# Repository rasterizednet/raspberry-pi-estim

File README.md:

# Raspberry Pi Estim

This repo includes kicad projects for the raspbi controller, and estim breakout, as well as the AVR source code for the estim breakout.

This is an untested prototype. More information can be found at [Schnizel Wolf: Raspberry PI Estim Breakout](https://schnitzelwolf.org/20/raspberry-pi-estim-breakout/)

Feel free to post ideas and recommendations on the Issue Board.

# LICENSE

CC0 1.0 Universal

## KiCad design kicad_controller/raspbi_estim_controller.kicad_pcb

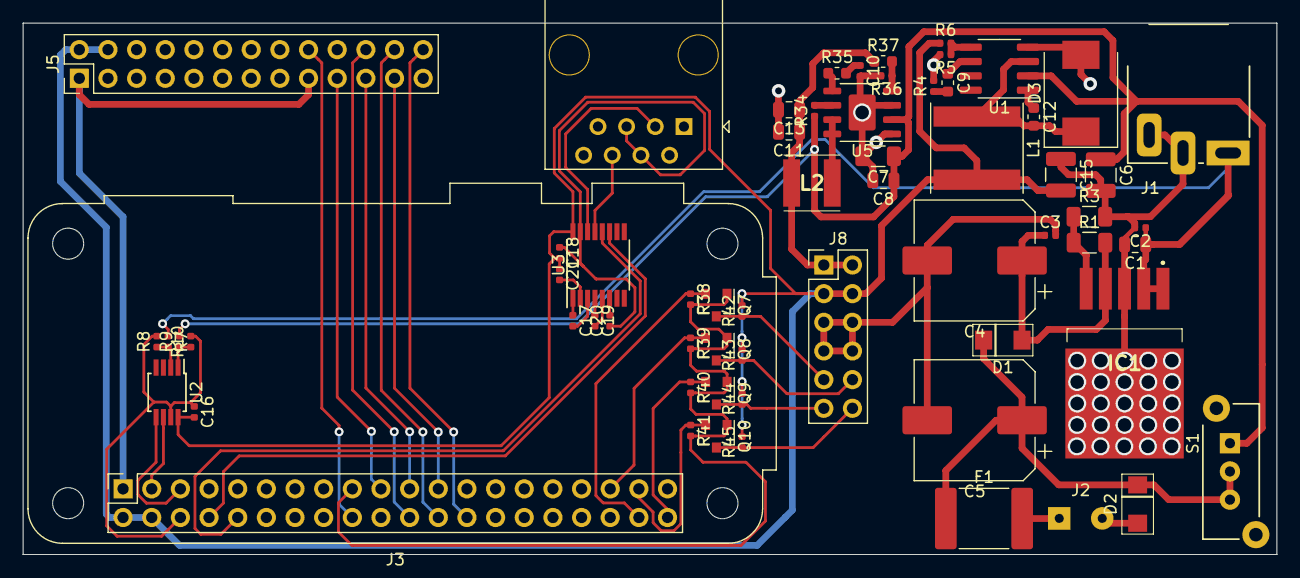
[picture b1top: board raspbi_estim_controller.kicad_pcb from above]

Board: 2 copper layers, 111.1 x 47.1 mm, 63 parts (0 on the bottom side), 49 nets.

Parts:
C1: 10uF; C_0805_2012Metric
C2, C3, C16, C18: 0.1uF; C_0402_1005Metric
C4, C5: 1000uF; CP_Elec_10x12.5
C6: 10uF 35V; C_1210_3225Metric
C7: 10uF 25VDC; C_1206_3216Metric
C8: 0.1uF 50VDC; C_0805_2012Metric
C9: 2.2nF 6.3V; C_0603_1608Metric
C10: 4700pF; C_0402_1005Metric
C11, C13: 22uF 16V; C_0805_2012Metric
C12: 10nF 50V; C_0603_1608Metric
C15: 22uF 10V; C_1210_3225Metric
C17, C19, C20, C21: 1uF; C_0402_1005Metric
D1, D2: 583-FM4004W-W; DO-214AC
D3: B340C/40V, 3A, SMB; D_SMC
F1: 1A Polyfuse; Fuse_2920_7451Metric
IC1: LD29300P2MTR
J1: Barrel_Jack_MountingPin; DJ_Jack_PJ-003A
J2: +12V Battery; SolderWirePad_1x02_P3.81mm_Drill0.8mm
J3: Raspberry_Pi_2_3; Raspberry_Pi_Zero_Socketed_THT_FaceDown_MountingHoles
J4: RJ45; RJ45_OST_PJ012-8P8CX_Vertical
J5: Conn_01x26_Male; PinHeader_2x13_P2.54mm_Vertical
J8: Conn_01x12_Male; estim_breakout
L1: 15uH 2.4A; L_Taiyo-Yuden_NR-80xx
L2: 4.7uH; SRN5040TA4R7M
Q7, Q8, Q9, Q10: BSS138; SOT-23
R1: 100K; R_1206_3216Metric
R3: 7.87K; R_1206_3216Metric
R4: 15K; R_0402_1005Metric
R5, R9, R36, R38, R39, R40, R41, R42, R43, R44, R45: 10K; R_0402_1005Metric
R6: 28.7K 1/16W 1%; R_0402_1005Metric
R7, R34: 100K; R_0402_1005Metric
R8: 33K; R_0402_1005Metric
R10: 6.8K; R_0402_1005Metric
R35: 12K; R_0603_1608Metric
R37: 105K; R_0603_1608Metric
S1: POWER; SW_E-Switch-LC-1258
U1: ACT4060ASH-T; SOP-8_3.76x4.96mm_P1.27mm
U2: MAX11607EUA; MSOP-8_3x3mm_P0.65mm
U3: MAX202; TSSOP-16_4.4x5mm_P0.65mm
U5: BD9C401EFJ-E2; HTSOP-8-1EP_3.9x4.9mm_P1.27mm_EP2.4x3.2mm

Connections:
+3V3: J3.1, J3.17, J5.1, J5.17, Q7.1, Q8.1, Q9.1, Q10.1, R38.2, R39.2, R40.2, R41.2
+5V: C15.2, C16.2, C18.2, C21.1, J3.2, J3.4, J5.2, J5.4, J8.3, J8.4, L1.2, R6.1, R42.2, R43.2, R44.2, R45.2, U2.8, U3.16
+9V: C11.1, C13.1, J8.1, J8.2, L2.2, R37.1
+VDC: C1.1, C2.1, IC1.1, IC1.2, J1.1, R7.1
+VSW: C6.1, C7.1, C8.1, R9.2, R34.1, S1.1, U1.2, U5.2
GND: C1.2, C2.2, C3.2, C4.2, C5.2, C6.2, C7.2, C8.2, C10.2, C11.2, C13.2, C15.1, C16.1, C18.1, C20.1, D2.2, D3.2, IC1.3, IC1.6, J1.2, J1.3, J2.2, J3.6, J3.9, J3.14, J3.20, J3.25, J3.30, J3.34, J3.39, J4.4, J4.5, J5.6, J5.9, J5.14, J5.20, J5.25, J8.5, J8.6, J8.7, J8.8, R3.2, R4.2, R5.2, R8.2, R10.2, R36.2, U1.4, U2.7, U3.15, U5.1, U5.3, U5.9
GPIO24: J3.18, J5.18
GPIO25: J3.22, J5.22
GPIO26: J3.37, Q10.2, R41.1
GPIO26-5V: J8.12, Q10.3, R45.1
MISO0: J3.21, J5.21
MISO1: J3.35, Q8.2, R39.1
MISO1-5V: J8.10, Q8.3, R43.1
MOSI0: J3.19, J5.19
MOSI1: J3.38, Q7.2, R38.1
MOSI1-5V: J8.9, Q7.3, R42.1
unnamed: C3.1, C4.1, D1.2, IC1.4, R1.2
unnamed: C5.1, D1.1, D2.1, F1.1, S1.2, S1.3
unnamed: C9.1, U1.6
unnamed: C9.2, R4.1
unnamed: C10.1, R35.2
unnamed: C12.1, U1.1
unnamed: C12.2, D3.1, L1.1, U1.3
unnamed: C17.1, U3.1
unnamed: C17.2, U3.3
unnamed: C19.1, U3.4
unnamed: C19.2, U3.5
unnamed: C20.2, U3.6
unnamed: C21.2, U3.2
unnamed: F1.2, J2.1
unnamed: IC1.5, R1.1, R3.1
unnamed: J4.3, U3.14
unnamed: J4.6, U3.13
unnamed: L2.1, U5.7, U5.8
unnamed: R5.1, R6.2, U1.5
unnamed: R7.2, R8.1, U2.2
unnamed: R9.1, R10.1, U2.1
unnamed: R34.2, U5.6
unnamed: R35.1, U5.5
unnamed: R36.1, R37.2, U5.4
RXD: J3.10, U3.12
SCL: J3.5, U2.5
SCLK0: J3.23, J5.23
SCLK1: J3.40, Q9.2, R40.1
SCLK1-5V: J8.11, Q9.3, R44.1
SDA: J3.3, U2.6
TXD: J3.8, U3.11
~CE0: J3.24, J5.24
~CE1: J3.26, J5.26

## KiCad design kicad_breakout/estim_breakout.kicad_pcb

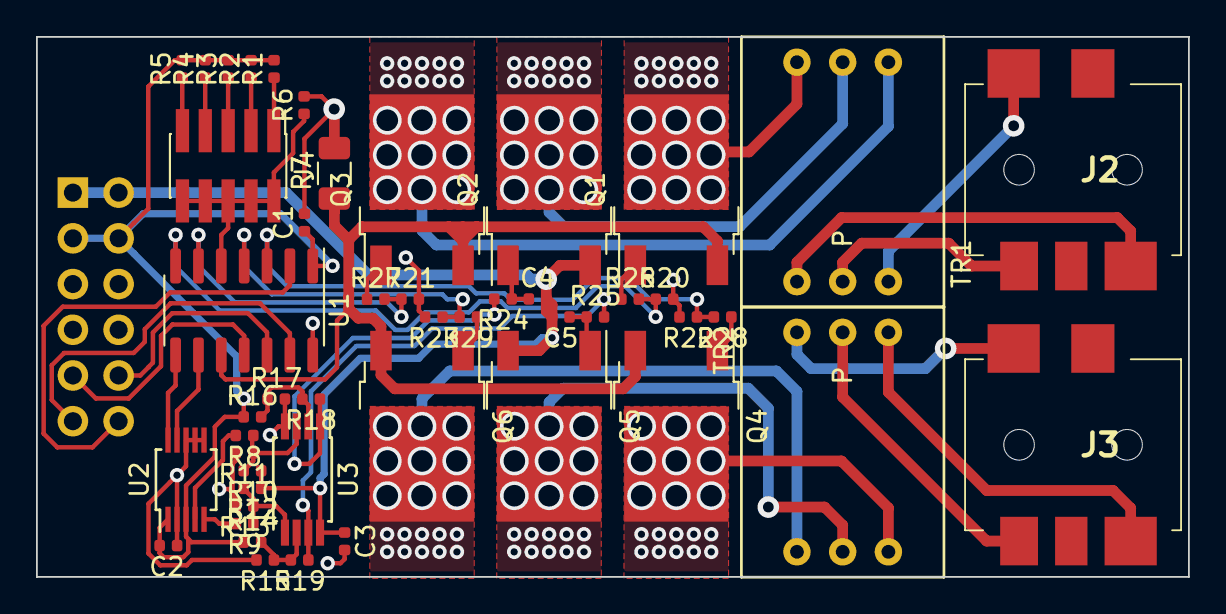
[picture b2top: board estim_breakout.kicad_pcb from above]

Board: 2 copper layers, 64.0 x 30.0 mm, 49 parts (1 on the bottom side), 46 nets.

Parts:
C1, C2, C3, C4, C5: 0.1uF; C_0402_1005Metric
J1: Conn_01x12_Female; PinSocket_2x06_P2.54mm_Vertical
J2: OUTPUT A; SJ13515SMTTR
J3: OUTPUT B; SJ13515SMTTR
J4: Conn_02x05_Odd_Even; PinHeader_2x05_P1.27mm_Vertical_SMD
Q1, Q3, Q4, Q6: IRLR120NTRPBF; TO-252-2
Q2, Q5: IRFR9024NTRPBF; TO-252-2
R1, R6: 1K; R_0402_1005Metric
R2: 2K; R_0402_1005Metric
R3: 4K; R_0402_1005Metric
R4: 8K; R_0402_1005Metric
R5: 16K; R_0402_1005Metric
R7: 2R 1/2W; R_1206_3216Metric
R8, R9, R10, R11, R12, R13, R14, R16, R18, R19, R20, R21, R22, R23: 100K; R_0402_1005Metric
R15, R17: 200K; R_0402_1005Metric
R24, R25, R26, R27, R28, R29: 10K; R_0402_1005Metric
TR1, TR2: 42TL004; 42TL
U1: ATtiny204-SS; SOIC-14_3.9x8.7mm_P1.27mm
U2: MCP47CMB12-E_UN; MSOP-10_3x3mm_P0.5mm
U3: LM358; TSSOP-8_4.4x3mm_P0.65mm

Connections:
+5VD: C1.1, C2.1, J1.3, J1.4, R1.2, R2.2, R3.2, R4.2, R5.2, R14.1, R16.1, U1.1, U2.1, U2.3
+9V1: C3.1, C4.2, C5.2, J1.1, J1.2, Q2.3, Q5.3, R10.1, R12.1, U3.8
AT-MISO: J1.10, U1.12
AT-MOSI: J1.9, U1.11
AT-PA0: Q1.3, Q3.3, Q4.3, Q6.3, R7.1, U1.10
AT-PA5: R22.1, R28.2, U1.3
AT-PA6: R23.1, R29.2, U1.4
AT-PA7: J4.2, J4.4, J4.6, J4.8, J4.10, R6.1, U1.5
AT-PB2: R20.1, R26.2, U1.7
AT-PB3: R21.1, R27.2, U1.6
AT-SCK: J1.11, U1.13
AT-SCL: U1.9, U2.9
AT-SDA: U1.8, U2.10
AT-~SS: J1.12, U1.2
GNDA: C1.2, C2.2, C3.2, J1.5, J1.6, J1.7, J1.8, R6.2, R7.2, R11.2, R13.2, R15.2, R17.2, R20.2, R21.2, R22.2, R23.2, U1.14, U2.2, U2.6, U2.7, U2.8, U3.4
unnamed: C4.1, Q2.1, R24.1
unnamed: C5.1, Q5.1, R25.1
unnamed: J2.R, TR1.2
unnamed: J2.S, TR1.1
unnamed: J2.T, TR1.3
unnamed: J3.R, TR2.2
unnamed: J3.S, TR2.1
unnamed: J3.T, TR2.3
unnamed: J4.1, R1.1
unnamed: J4.3, R2.1
unnamed: J4.5, R3.1
unnamed: J4.7, R4.1
unnamed: J4.9, R5.1
unnamed: Q1.1, R26.1
unnamed: Q1.2, TR1.6
unnamed: Q2.2, TR1.5
unnamed: Q3.1, R27.1
unnamed: Q3.2, TR1.4
unnamed: Q4.1, R28.1
unnamed: Q4.2, TR2.6
unnamed: Q5.2, TR2.5
unnamed: Q6.1, R29.1
unnamed: Q6.2, TR2.4
unnamed: R8.2, U2.4
unnamed: R9.2, U2.5
unnamed: R8.1, R10.2, R11.1, U3.3
unnamed: R9.1, R12.2, R13.1, U3.5
unnamed: R14.2, R15.1, R19.2, U3.6
unnamed: R16.2, R17.1, R18.2, U3.2
unnamed: R18.1, R24.2, U3.1
unnamed: R19.1, R25.2, U3.7
